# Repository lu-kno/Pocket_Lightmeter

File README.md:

# Pocket Light Meter

Lightmeter built from an ATTiny 85 and a BH1750FVI light sensor.
3 Buttons used to control the device.
The device is powered by a 3.7V LiPo battery.

Circuit Schematics and PCB design files are available in the `EAGLE` folder.

# Other

`esp_lightmeter` folder is a work in progress to build a lightmeter using an ESP8266 and a BH1750FVI light sensor. STALE

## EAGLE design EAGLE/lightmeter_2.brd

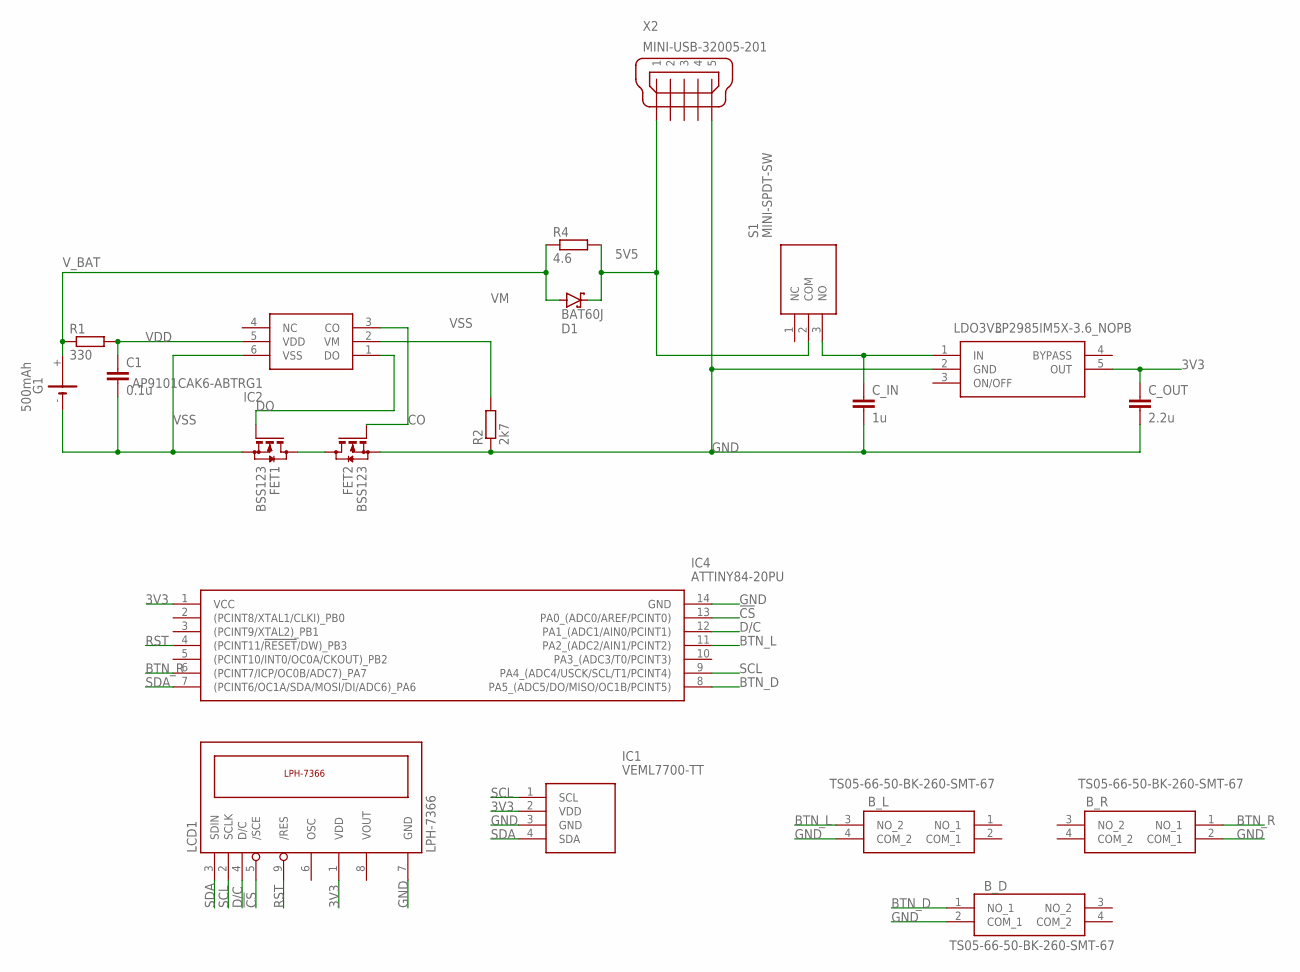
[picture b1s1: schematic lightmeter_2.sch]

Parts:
B_D: TS05-66-50-BK-260-SMT-67; TS056650BK260SMT67
B_L: TS05-66-50-BK-260-SMT-67; TS056650BK260SMT67
B_R: TS05-66-50-BK-260-SMT-67; TS056650BK260SMT67
C1: 0.1u; C3216
C_IN: 1u; C3216
C_OUT: 2.2u; C3216
D1: BAT60J; SOD323_ST
FET1, FET2: BSS123; SOT23
G1: 500mAh; CR1/2
IC1: VEML7700-TT; VEML7700
IC2: AP9101CAK6-ABTRG1; SOT95P285X140-6N
IC4: ATTINY84-20PU; DIP794W56P254L1918H533Q14N
LCD1: LPH-7366
LDO3V3: LP2985IM5X-3.6_NOPB; SOT95P280X145-5N
R1: 330; R3216W
R2: 2k7; R3216W
R4: 4.6; R3216W
S1: MINI-SPDT-SW; MINISPDTSW
X2: MINI-USB-32005-201; 32005-201

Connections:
3V3: C_OUT.1, IC1.2 (VDD), IC4.1 (VCC), LCD1.1 (VDD), LDO3V3.5 (OUT)
5V5: D1.C, R4.2, S1.2 (COM), X2.1
!CS: IC4.13 (PA0_(ADC0/AREF/PCINT0)), LCD1.5 (/SCE)
BTN_D: B_D.1 (NO_1), IC4.8 (PA5_(ADC5/DO/MISO/OC1B/PCINT5))
BTN_L: B_L.3 (NO_2), IC4.11 (PA2_(ADC2/AIN1/PCINT2))
BTN_R: B_R.1 (NO_1), IC4.6 ((PCINT7/ICP/OC0B/ADC7)_PA7)
CO: FET2.1 (G), IC2.3 (CO)
D/C: IC4.12 (PA1_(ADC1/AIN0/PCINT1)), LCD1.4 (D/C)
DO: FET1.1 (G), IC2.1 (DO)
GND: B_D.2 (COM_1), B_L.4 (COM_2), B_R.2 (COM_1), C_IN.2, C_OUT.2, FET2.2 (S), IC1.3 (GND), IC4.14 (GND), LCD1.7 (GND), LDO3V3.2 (GND), R2.1, X2.5
unnamed: C_IN.1, LDO3V3.1 (IN), S1.3 (NO)
unnamed: FET1.3 (D), FET2.3 (D)
RST: IC4.4 ((PCINT11/!RESET!/DW)_PB3), LCD1.9 (/RES)
SCL: IC1.1 (SCL), IC4.9 (PA4_(ADC4/USCK/SCL/T1/PCINT4)), LCD1.2 (SCLK)
SDA: IC1.4 (SDA), IC4.7 ((PCINT6/OC1A/SDA/MOSI/DI/ADC6)_PA6), LCD1.3 (SDIN)
VDD: C1.1, IC2.5 (VDD), R1.2
VM: IC2.2 (VM), R2.2
VSS: C1.2, FET1.2 (S), G1.-, IC2.6 (VSS)
V_BAT: D1.A, G1.+, R1.1, R4.1

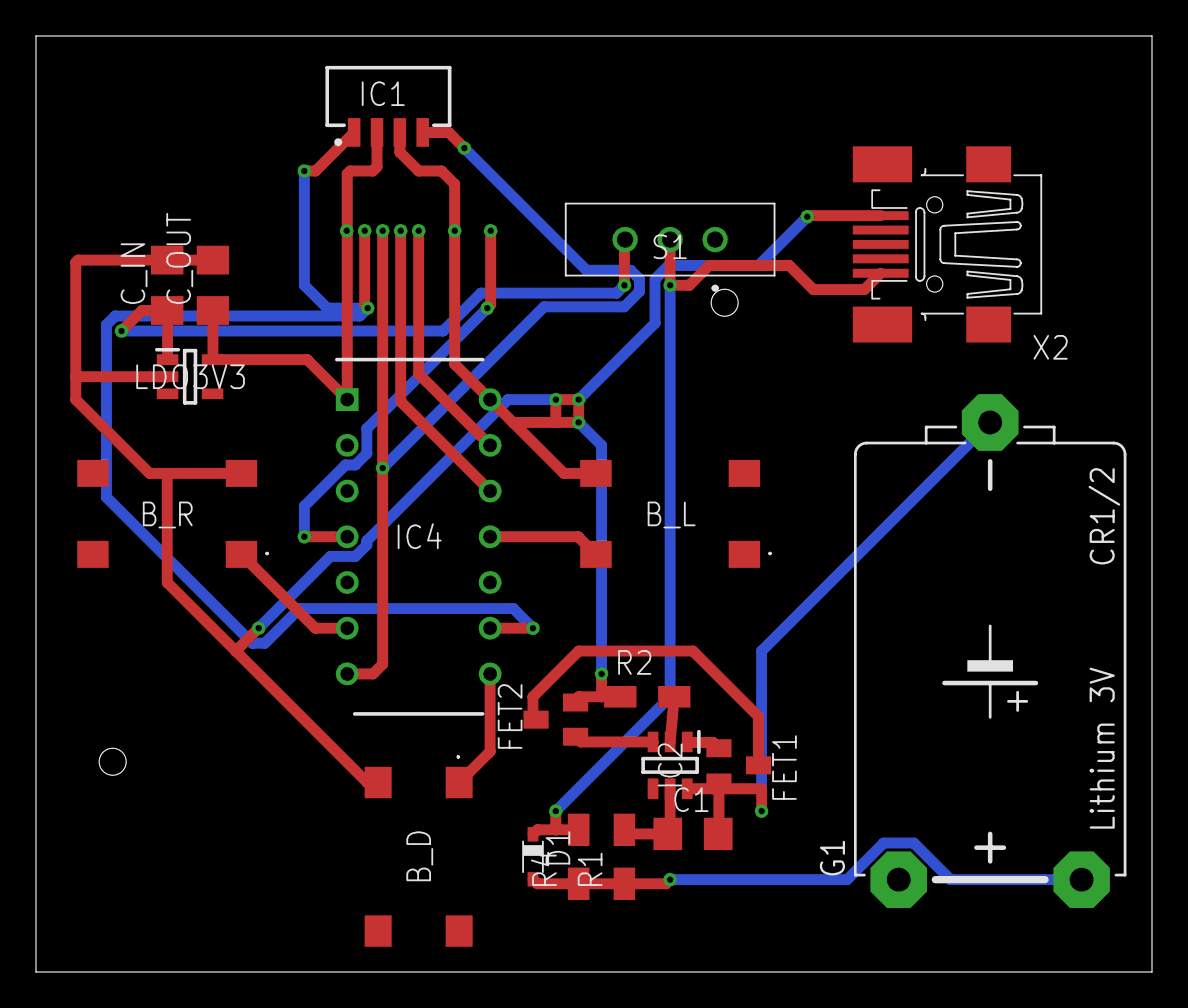
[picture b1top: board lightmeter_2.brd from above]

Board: 2 copper layers, 62.0 x 52.0 mm, 20 parts (1 on the bottom side), 19 nets.

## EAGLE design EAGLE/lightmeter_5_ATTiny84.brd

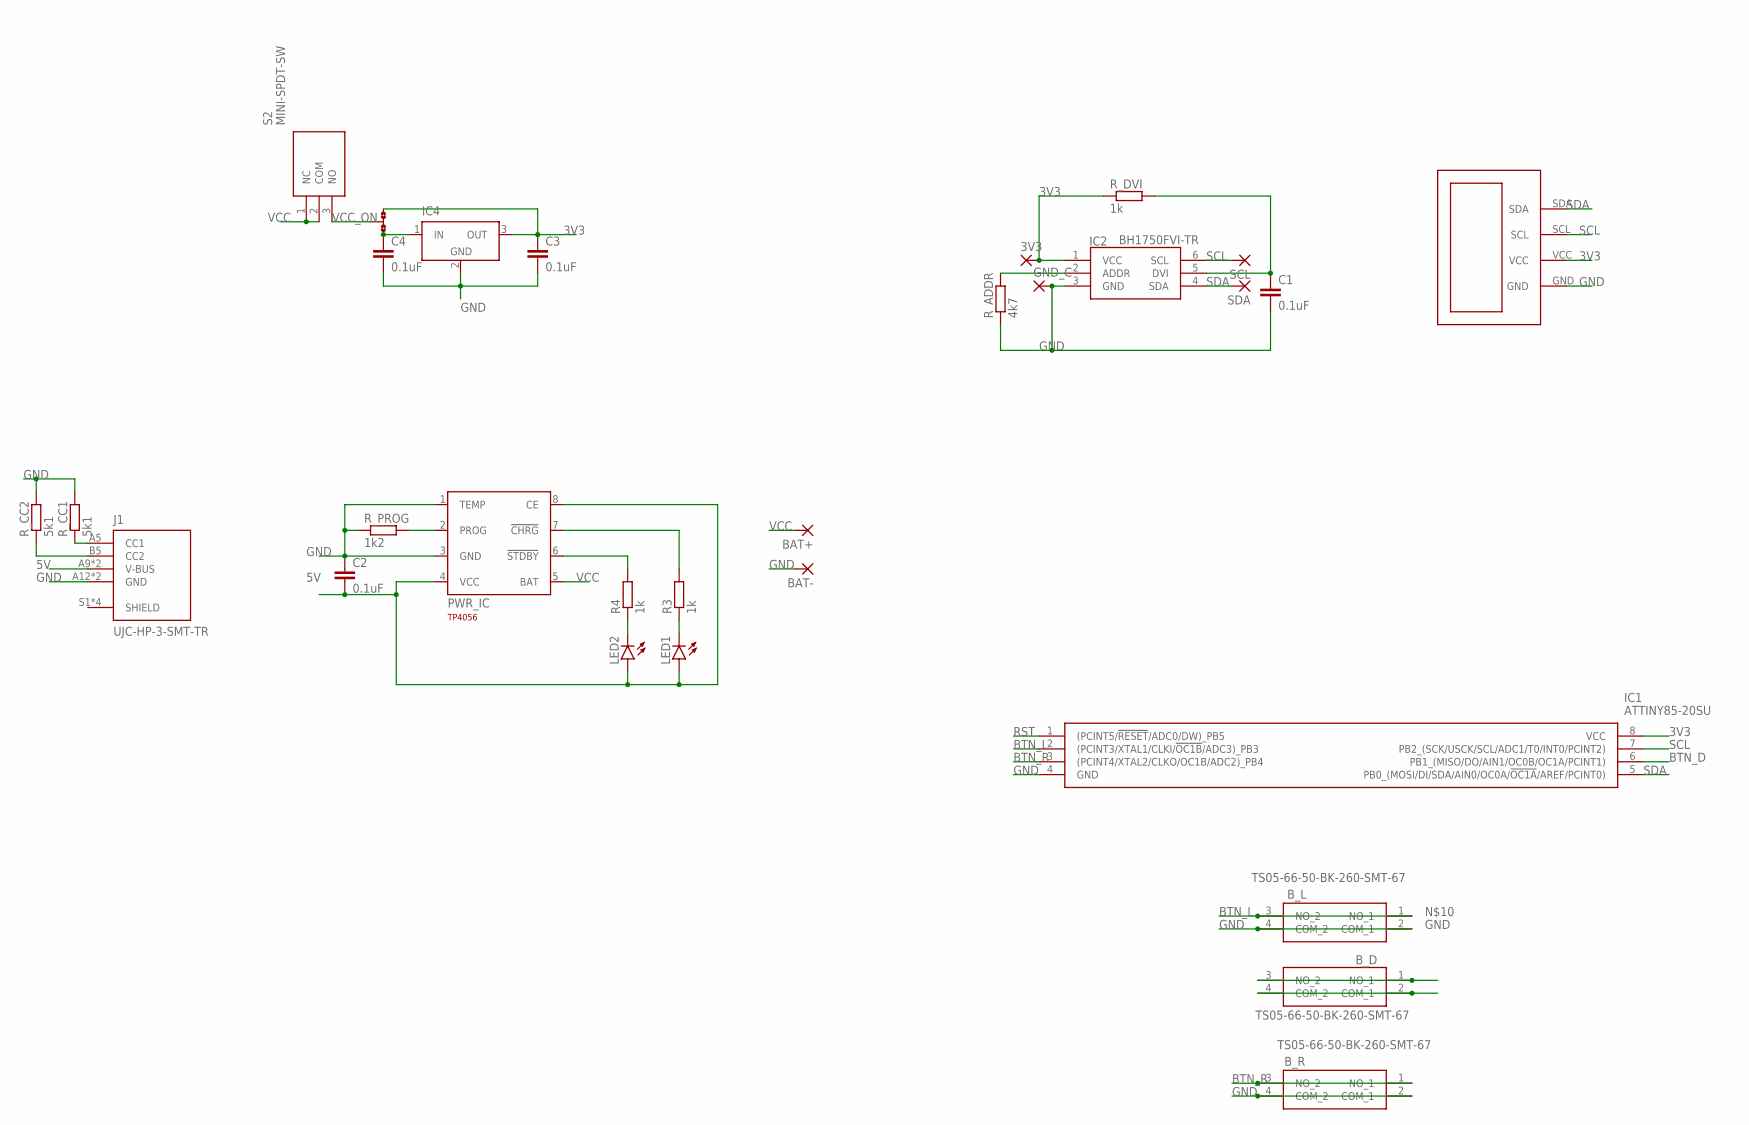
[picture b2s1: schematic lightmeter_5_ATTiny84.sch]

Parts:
3V3: 1,6/0,8
BAT+: WIREPADSMD1,27-254; SMD1,27-2,54
BAT-: WIREPADSMD1,27-254; SMD1,27-2,54
B_D: TS05-66-50-BK-260-SMT-67; TS056650BK260SMT67
B_L: TS05-66-50-BK-260-SMT-67; TS056650BK260SMT67
B_R: TS05-66-50-BK-260-SMT-67; TS056650BK260SMT67
C1, C2, C3, C4: 0.1uF; C0805K
GND_C: 1,6/0,8
IC1: ATTINY85-20SU; SOIC127P798X216-8N
IC2: BH1750FVI-TR; WSOF6
IC4: LT1129CST5; SOT223
J1: UJC-HP-3-SMT-TR; CUI_UJC-HP-3-SMT-TR
JMP1: 0R-JUMPB; B0R-JMP
LED1, LED2: LEDCHIPLED_1206; CHIPLED_1206
PWR_IC: TP4056; SOT23-8
R3, R4: 1k; R0805
R_ADDR: 4k7; R0805
R_CC1, R_CC2: 5k1; R0805
R_DVI: 1k; R0805
R_PROG: 1k2; R0805
S2: MINI-SPDT-SW; MINISPDTSW
SCL: 1,6/0,8
SDA: 1,6/0,8
U$1: I2C_OLED_128X64; I2C_OLED_128X64_BREAKOUT

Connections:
3V3: 3V3.1, C3.1, IC1.8 (VCC), IC2.1 (VCC), IC4.3 (OUT), JMP1.3, R_DVI.1, U$1.VCC
5V: C2.2, J1.A9 (V-BUS), J1.B9 (V-BUS), LED1.A, LED2.A, PWR_IC.4 (VCC), PWR_IC.8 (CE)
BTN_D: IC1.6 (PB1_(MISO/DO/AIN1/OC0B/OC1A/PCINT1))
BTN_L: B_L.1 (NO_1), B_L.3 (NO_2), IC1.2 ((PCINT3/XTAL1/CLKI/!OC1B!/ADC3)_PB3)
BTN_R: B_R.1 (NO_1), B_R.3 (NO_2), IC1.3 ((PCINT4/XTAL2/CLKO/OC1B/ADC2)_PB4)
GND: BAT-.1, B_D.2 (COM_1), B_D.4 (COM_2), B_L.2 (COM_1), B_L.4 (COM_2), B_R.2 (COM_1), B_R.4 (COM_2), C1.2, C2.1, C3.2, C4.2, GND_C.1, IC1.4 (GND), IC2.3 (GND), IC4.2 (GND), IC4.4 (GND), J1.A12 (GND), J1.B12 (GND), PWR_IC.1 (TEMP), PWR_IC.3 (GND), R_ADDR.1, R_CC1.2, R_CC2.2, R_PROG.1, U$1.GND
unnamed: C1.1, IC2.5 (DVI), R_DVI.2
unnamed: IC2.2 (ADDR), R_ADDR.2
unnamed: J1.B5 (CC2), R_CC2.1
unnamed: PWR_IC.6 (!STDBY), R4.2
unnamed: PWR_IC.7 (!CHRG), R3.2
unnamed: LED2.C, R4.1
unnamed: LED1.C, R3.1
unnamed: J1.A5 (CC1), R_CC1.1
unnamed: PWR_IC.2 (PROG), R_PROG.2
unnamed: B_D.1 (NO_1), B_D.3 (NO_2)
unnamed: C4.1, IC4.1 (IN), JMP1.1
RST: IC1.1 ((PCINT5/!RESET!/ADC0/DW)_PB5)
SCL: IC1.7 (PB2_(SCK/USCK/SCL/ADC1/T0/INT0/PCINT2)), IC2.6 (SCL), SCL.1, U$1.SCL
SDA: IC1.5 (PB0_(MOSI/DI/SDA/AIN0/OC0A/!OC1A!/AREF/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), IC2.4 (SDA), SDA.1, U$1.SDA
VCC: BAT+.1, PWR_IC.5 (BAT), S2.1 (NC), S2.2 (COM)
VCC_ON: JMP1.2, S2.3 (NO)

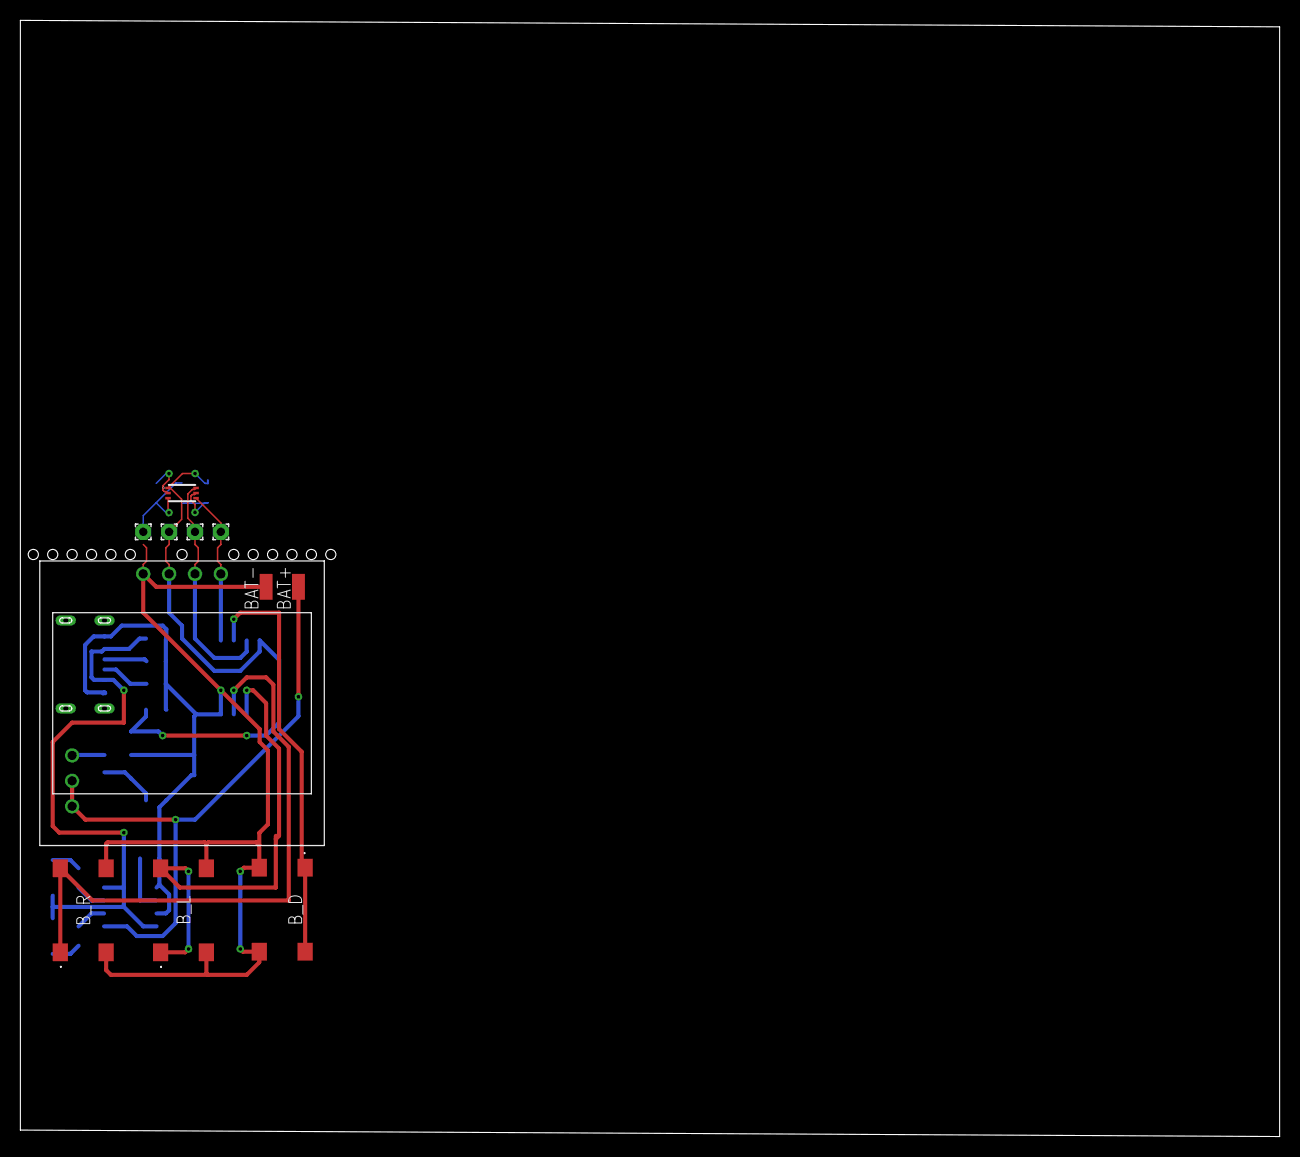
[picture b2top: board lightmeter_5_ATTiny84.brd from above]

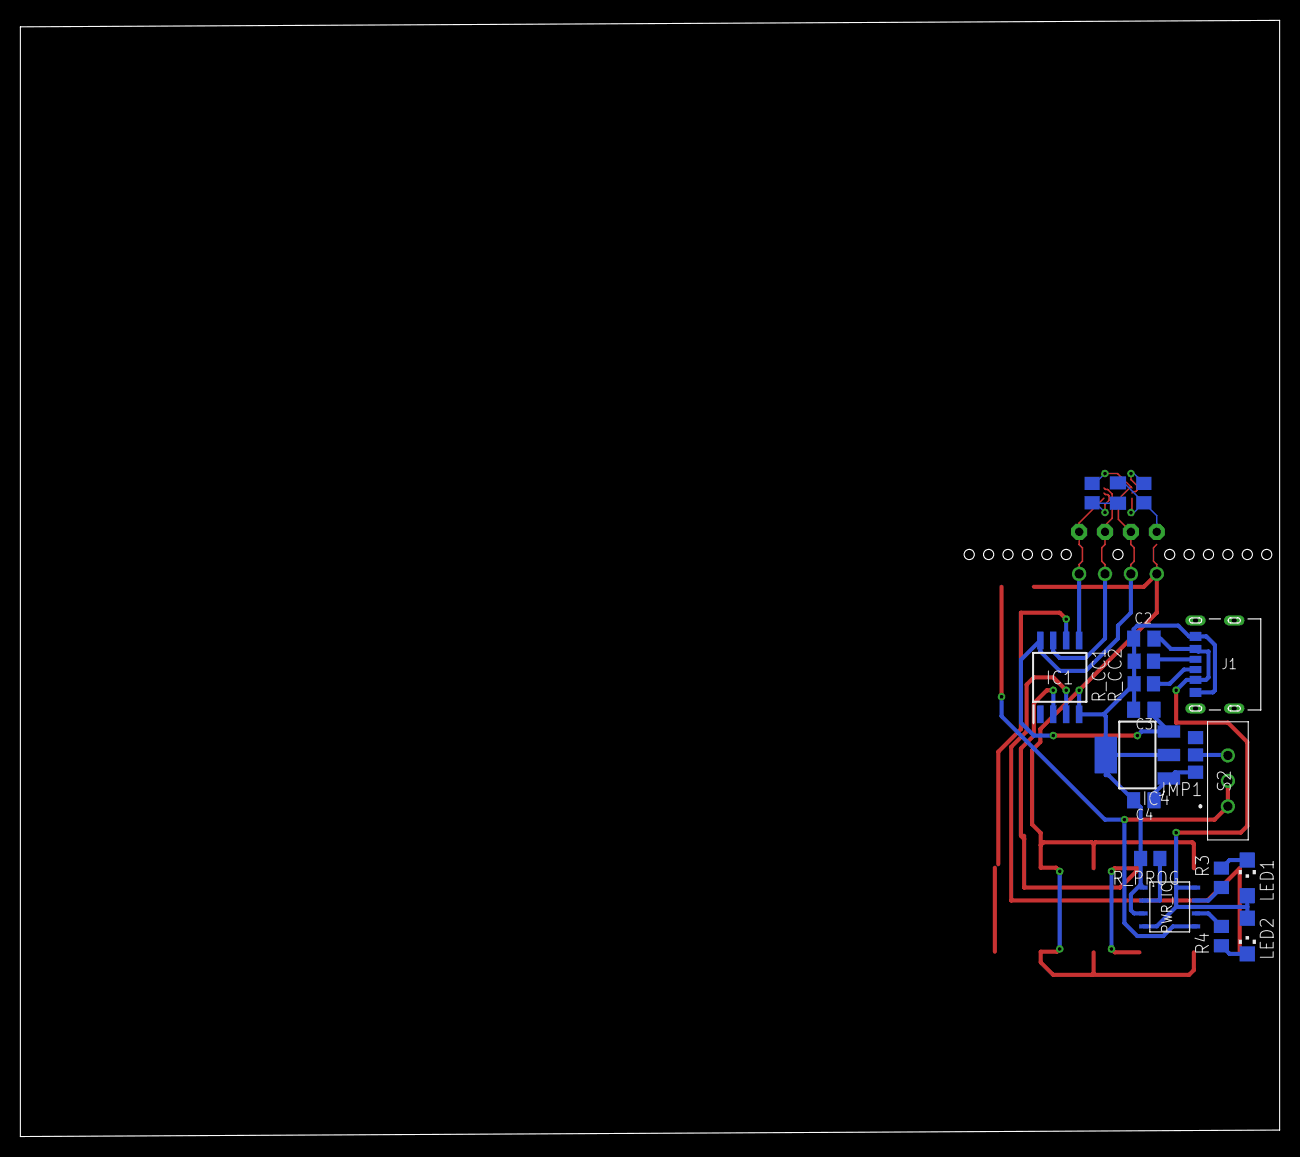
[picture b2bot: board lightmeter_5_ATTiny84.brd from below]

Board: 2 copper layers, 123.6 x 109.6 mm, 30 parts (19 on the bottom side), 20 nets.

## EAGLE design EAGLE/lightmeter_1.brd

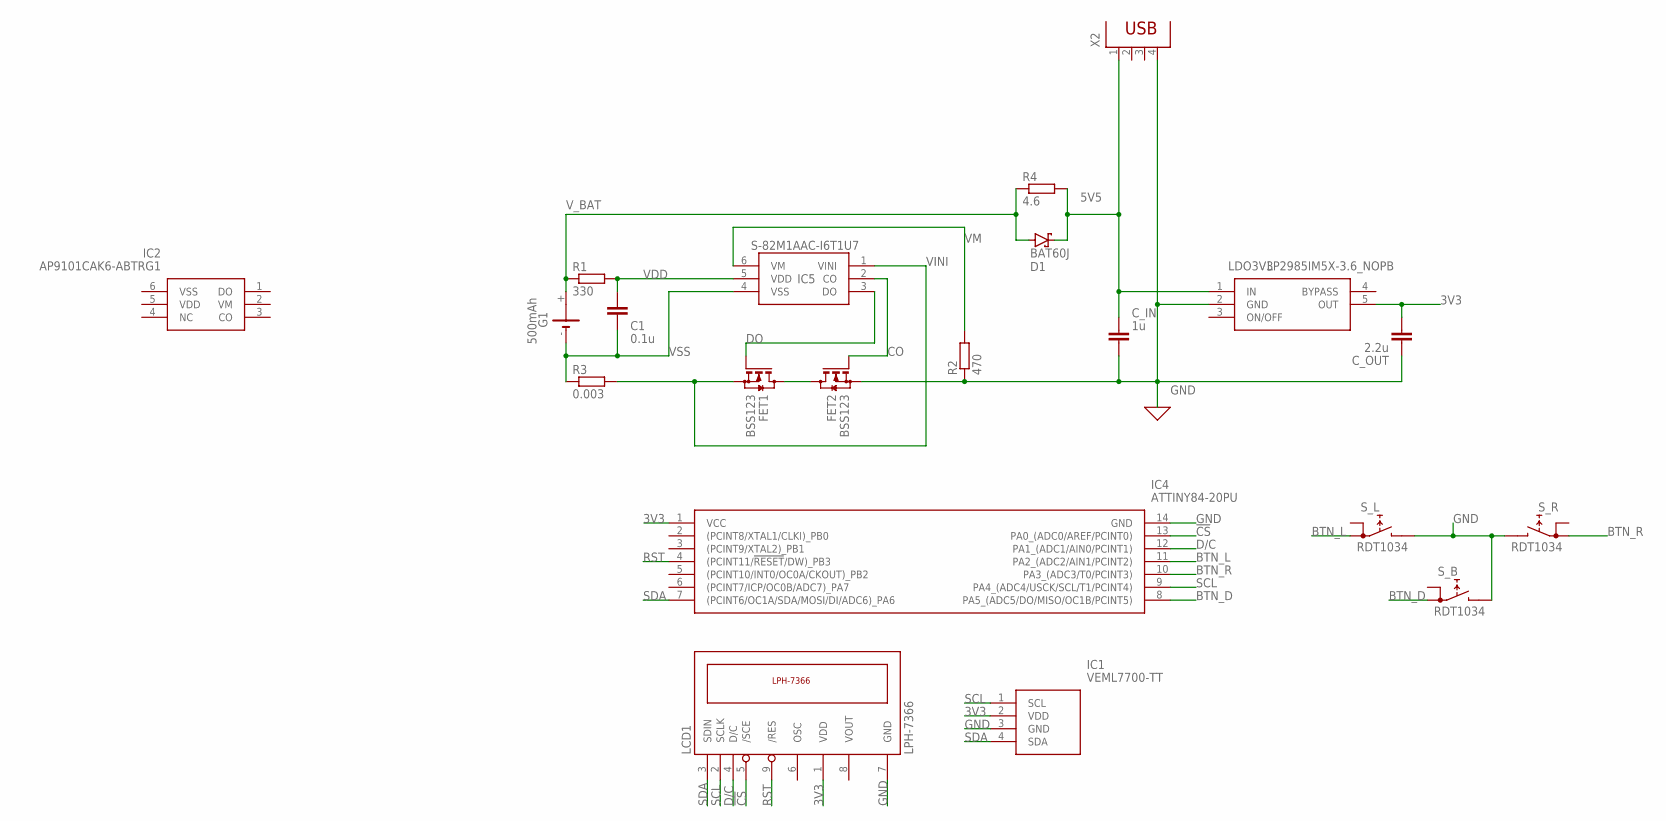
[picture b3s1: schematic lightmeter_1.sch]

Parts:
D1: BAT60J; SOD323_ST
FET1, FET2: BSS123; SOT23
G1: 500mAh; CR1/2
IC1: VEML7700-TT; VEML7700
IC2: AP9101CAK6-ABTRG1; SOT95P285X140-6N
IC4: ATTINY84-20PU; DIP794W56P254L1918H533Q14N
IC5: S-82M1AAC-I6T1U7; SON50P170X157X48-6N
LCD1: LPH-7366
LDO3V3: LP2985IM5X-3.6_NOPB; SOT95P280X145-5N
R1: 330; R3216W
R2: 470; R3216W
R3: 0.003; R3216W
R4: 4.6; R3216W
S_B: RDT1034
S_L: RDT1034
S_R: RDT1034
X2: PN87520

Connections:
3V3: IC1.2 (VDD), IC4.1 (VCC), LCD1.1 (VDD), LDO3V3.5 (OUT)
5V5: D1.C, LDO3V3.1 (IN), R4.2, X2.1
!CS: IC4.13 (PA0_(ADC0/AREF/PCINT0)), LCD1.5 (/SCE)
BTN_D: IC4.8 (PA5_(ADC5/DO/MISO/OC1B/PCINT5)), S_B.A1
BTN_L: IC4.11 (PA2_(ADC2/AIN1/PCINT2)), S_L.A1
BTN_R: IC4.10 (PA3_(ADC3/T0/PCINT3)), S_R.A1
CO: FET2.1 (G), IC5.2 (CO)
D/C: IC4.12 (PA1_(ADC1/AIN0/PCINT1)), LCD1.4 (D/C)
DO: FET1.1 (G), IC5.3 (DO)
GND: FET2.2 (S), IC1.3 (GND), IC4.14 (GND), LCD1.7 (GND), LDO3V3.2 (GND), R2.1, S_B.B, S_L.B, S_R.B, X2.4
unnamed: FET1.3 (D), FET2.3 (D)
RST: IC4.4 ((PCINT11/!RESET!/DW)_PB3), LCD1.9 (/RES)
SCL: IC1.1 (SCL), IC4.9 (PA4_(ADC4/USCK/SCL/T1/PCINT4)), LCD1.2 (SCLK)
SDA: IC1.4 (SDA), IC4.7 ((PCINT6/OC1A/SDA/MOSI/DI/ADC6)_PA6), LCD1.3 (SDIN)
VDD: IC5.5 (VDD), R1.2
VINI: FET1.2 (S), IC5.1 (VINI), R3.2
VM: IC5.6 (VM), R2.2
VSS: G1.-, IC5.4 (VSS), R3.1
V_BAT: D1.A, G1.+, R1.1, R4.1

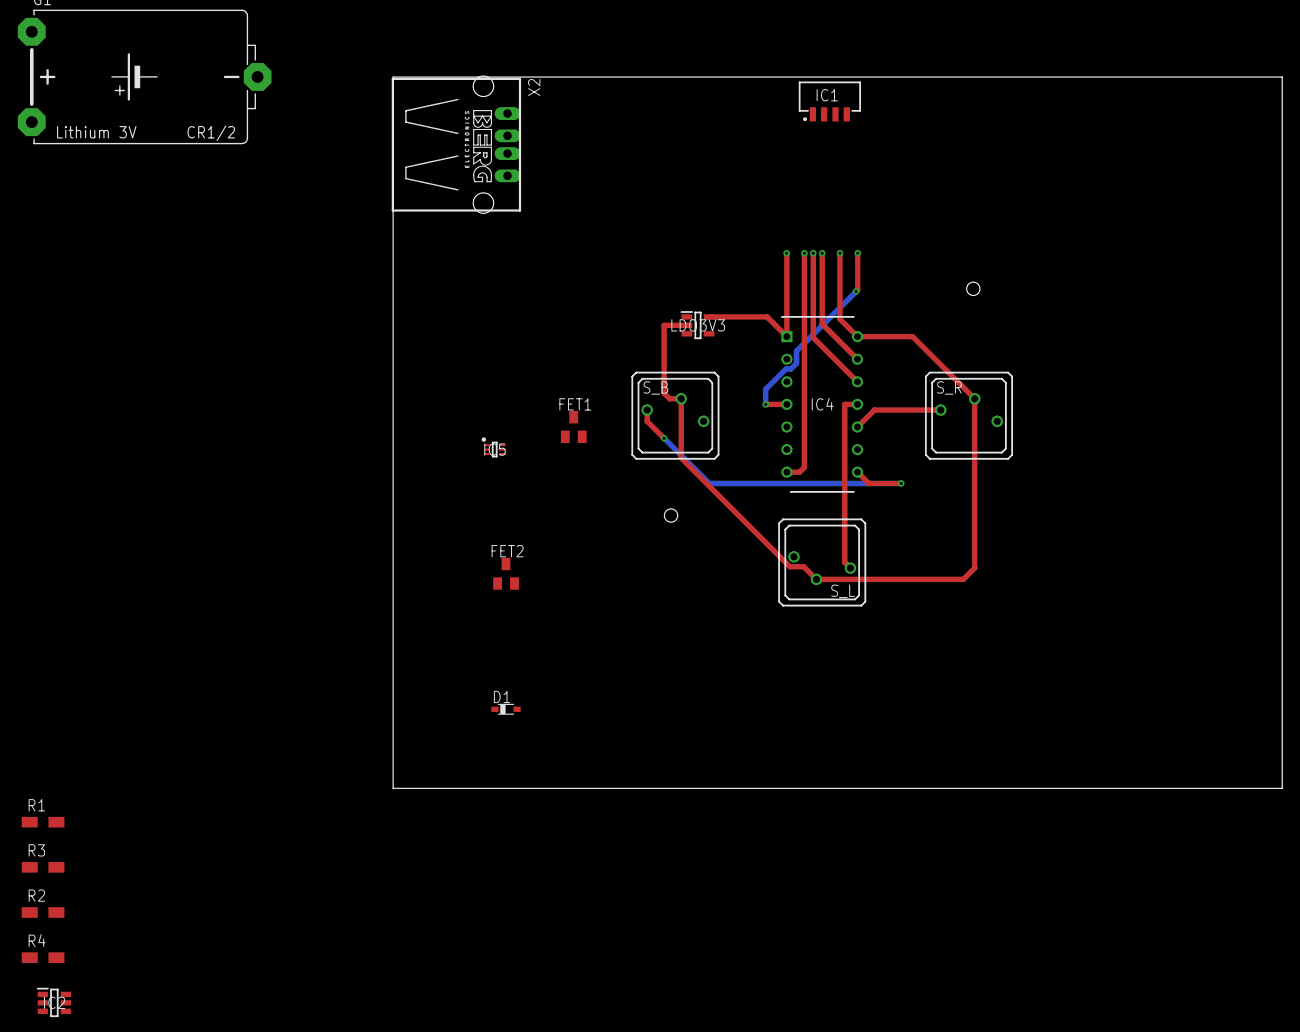
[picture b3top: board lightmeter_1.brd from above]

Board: 2 copper layers, 100.0 x 80.0 mm, 18 parts (1 on the bottom side), 19 nets.

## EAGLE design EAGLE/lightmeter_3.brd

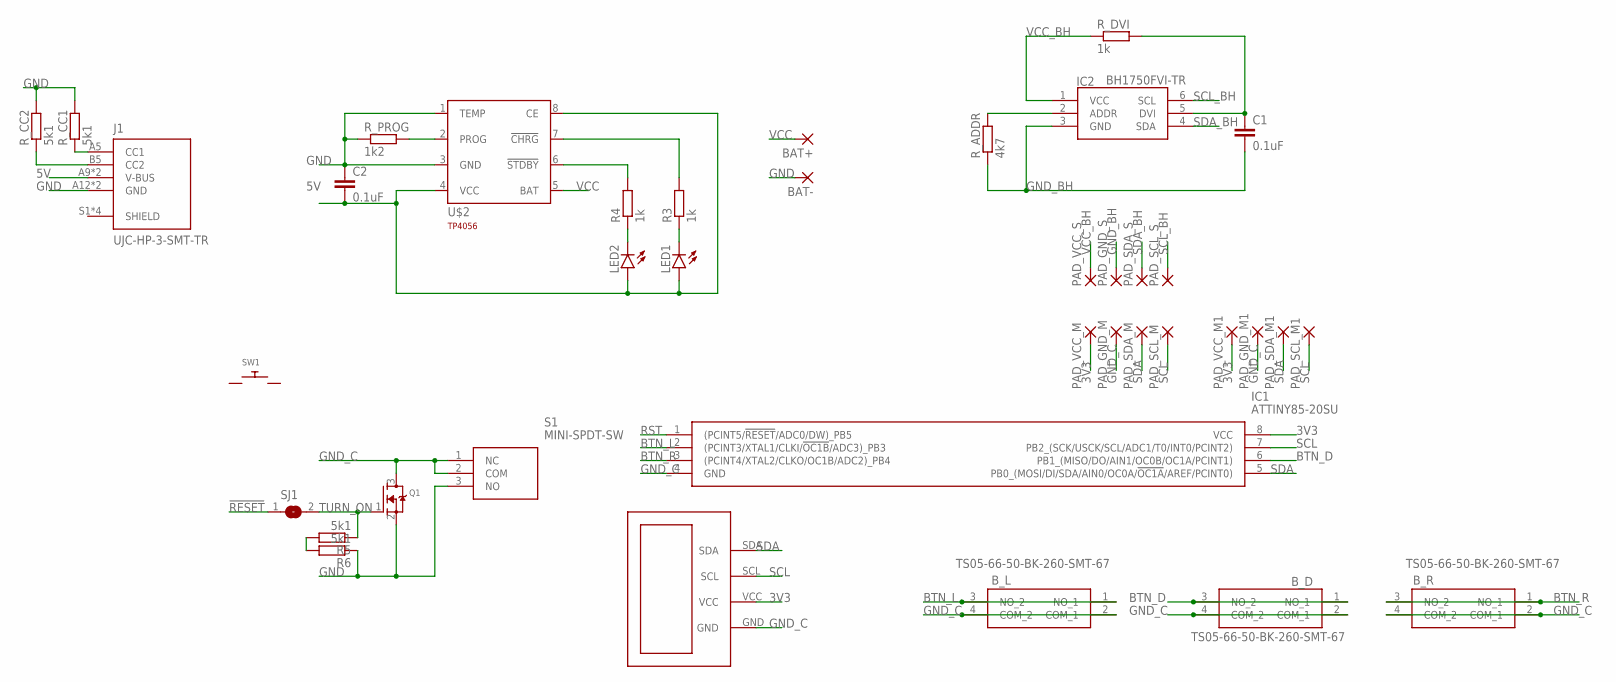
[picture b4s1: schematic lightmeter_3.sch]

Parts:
BAT+: WIREPADSMD1,27-254; SMD1,27-2,54
BAT-: WIREPADSMD1,27-254; SMD1,27-2,54
B_D: TS05-66-50-BK-260-SMT-67; TS056650BK260SMT67
B_L: TS05-66-50-BK-260-SMT-67; TS056650BK260SMT67
B_R: TS05-66-50-BK-260-SMT-67; TS056650BK260SMT67
C1, C2: 0.1uF; C0805K
IC1: ATTINY85-20SU; SOIC127P798X216-8N
IC2: BH1750FVI-TR; WSOF6
J1: UJC-HP-3-SMT-TR; CUI_UJC-HP-3-SMT-TR
LED1, LED2: LEDCHIPLED_1206; CHIPLED_1206
PAD_GND_M, PAD_GND_M1: SMD5; SMD2,54-5,08
PAD_GND_S: SMD5; SMD2,54-5,08
PAD_SCL_M, PAD_SCL_M1: SMD5; SMD2,54-5,08
PAD_SCL_S: SMD5; SMD2,54-5,08
PAD_SDA_M, PAD_SDA_M1: SMD5; SMD2,54-5,08
PAD_SDA_S: SMD5; SMD2,54-5,08
PAD_VCC_M, PAD_VCC_M1: SMD5; SMD2,54-5,08
PAD_VCC_S: SMD5; SMD2,54-5,08
Q1: MOSFET-NREFLOW; SOT23
R3, R4: 1k; R0805
R5, R6: 5k1; R0805
R_ADDR: 4k7; R0805
R_CC1, R_CC2: 5k1; R0805
R_DVI: 1k; R0805
R_PROG: 1k2; R0805
S1: MINI-SPDT-SW; MINISPDTSW
SJ1: SJ
SW1: SWITCH_PUSHBUTTONEVQ-PE; TACT_PANA-EVQ
U$1: I2C_OLED_128X64; I2C_OLED_128X64_BREAKOUT
U$2: TP4056; SOT23-8

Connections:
3V3: IC1.8 (VCC), PAD_VCC_M.1, PAD_VCC_M1.1, U$1.VCC
5V: C2.2, J1.A9 (V-BUS), J1.B9 (V-BUS), LED1.A, LED2.A, U$2.4 (VCC), U$2.8 (CE)
!RESET: SJ1.1
BTN_D: B_D.1 (NO_1), B_D.3 (NO_2), IC1.6 (PB1_(MISO/DO/AIN1/OC0B/OC1A/PCINT1))
BTN_L: B_L.1 (NO_1), B_L.3 (NO_2), IC1.2 ((PCINT3/XTAL1/CLKI/!OC1B!/ADC3)_PB3)
BTN_R: B_R.1 (NO_1), B_R.3 (NO_2), IC1.3 ((PCINT4/XTAL2/CLKO/OC1B/ADC2)_PB4)
GND: BAT-.1, C2.1, J1.A12 (GND), J1.B12 (GND), Q1.2 (S), R6.1, R_CC1.2, R_CC2.2, R_PROG.1, S1.3 (NO), U$2.1 (TEMP), U$2.3 (GND)
GND_BH: C1.2, IC2.3 (GND), PAD_GND_S.1, R_ADDR.1
GND_C: B_D.2 (COM_1), B_D.4 (COM_2), B_L.2 (COM_1), B_L.4 (COM_2), B_R.2 (COM_1), B_R.4 (COM_2), IC1.4 (GND), PAD_GND_M.1, PAD_GND_M1.1, Q1.3 (D), S1.1 (NC), S1.2 (COM), U$1.GND
unnamed: C1.1, IC2.5 (DVI), R_DVI.2
unnamed: IC2.2 (ADDR), R_ADDR.2
unnamed: J1.B5 (CC2), R_CC2.1
unnamed: R4.2, U$2.6 (!STDBY)
unnamed: R3.2, U$2.7 (!CHRG)
unnamed: LED2.C, R4.1
unnamed: LED1.C, R3.1
unnamed: J1.A5 (CC1), R_CC1.1
unnamed: R_PROG.2, U$2.2 (PROG)
unnamed: R5.2, R6.2
RST: IC1.1 ((PCINT5/!RESET!/ADC0/DW)_PB5)
SCL: IC1.7 (PB2_(SCK/USCK/SCL/ADC1/T0/INT0/PCINT2)), PAD_SCL_M.1, PAD_SCL_M1.1, U$1.SCL
SCL_BH: IC2.6 (SCL), PAD_SCL_S.1
SDA: IC1.5 (PB0_(MOSI/DI/SDA/AIN0/OC0A/!OC1A!/AREF/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), PAD_SDA_M.1, PAD_SDA_M1.1, U$1.SDA
SDA_BH: IC2.4 (SDA), PAD_SDA_S.1
TURN_ON: Q1.1 (G), R5.1, SJ1.2
VCC: BAT+.1, U$2.5 (BAT)
VCC_BH: IC2.1 (VCC), PAD_VCC_S.1, R_DVI.1

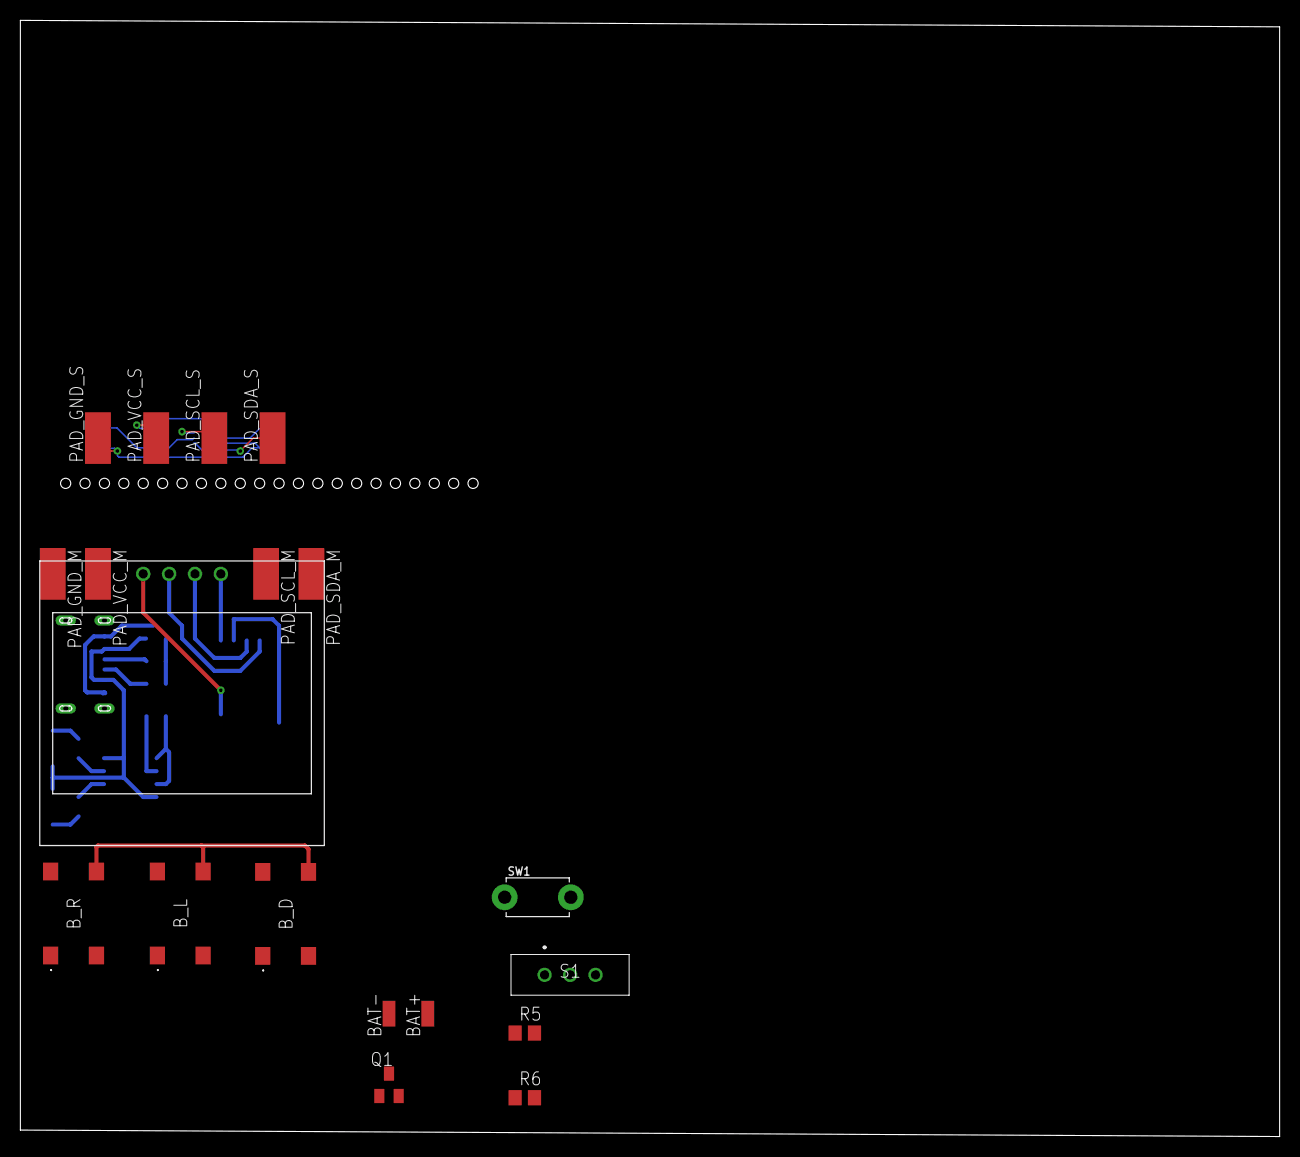
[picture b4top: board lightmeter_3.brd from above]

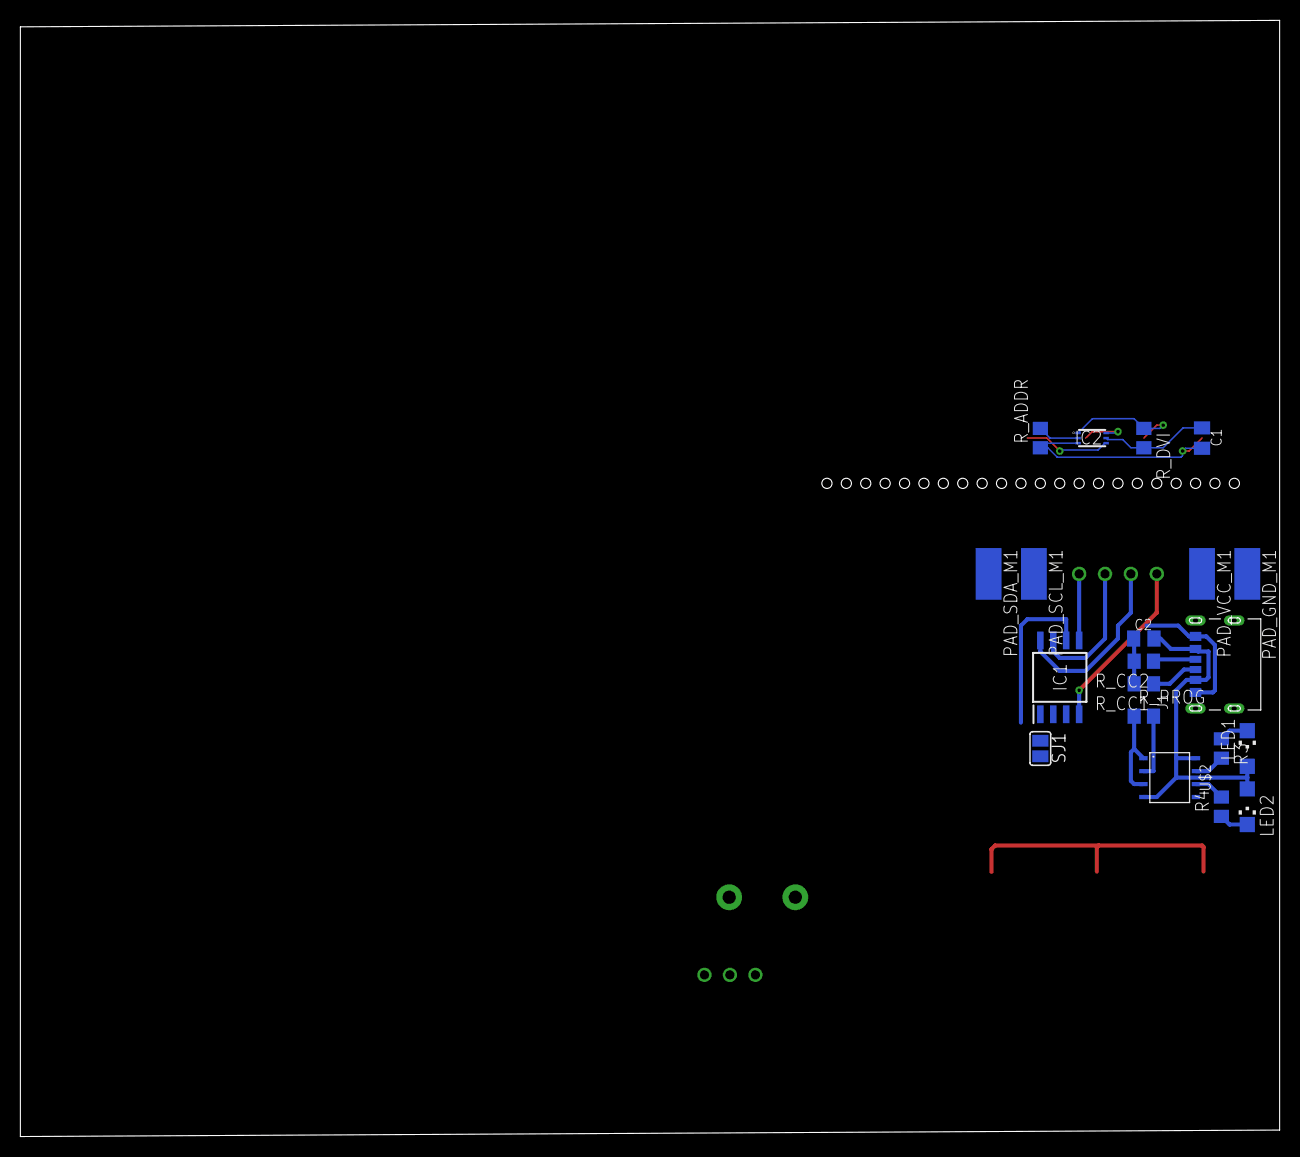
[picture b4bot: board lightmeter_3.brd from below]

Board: 2 copper layers, 123.6 x 109.6 mm, 39 parts (20 on the bottom side), 25 nets.

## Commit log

2023-02-25 My new Initial Commit
